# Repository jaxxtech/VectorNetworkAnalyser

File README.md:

View this project on [CADLAB.io](https://cadlab.io/project/1782). 

# VectorNetworkAnalyser

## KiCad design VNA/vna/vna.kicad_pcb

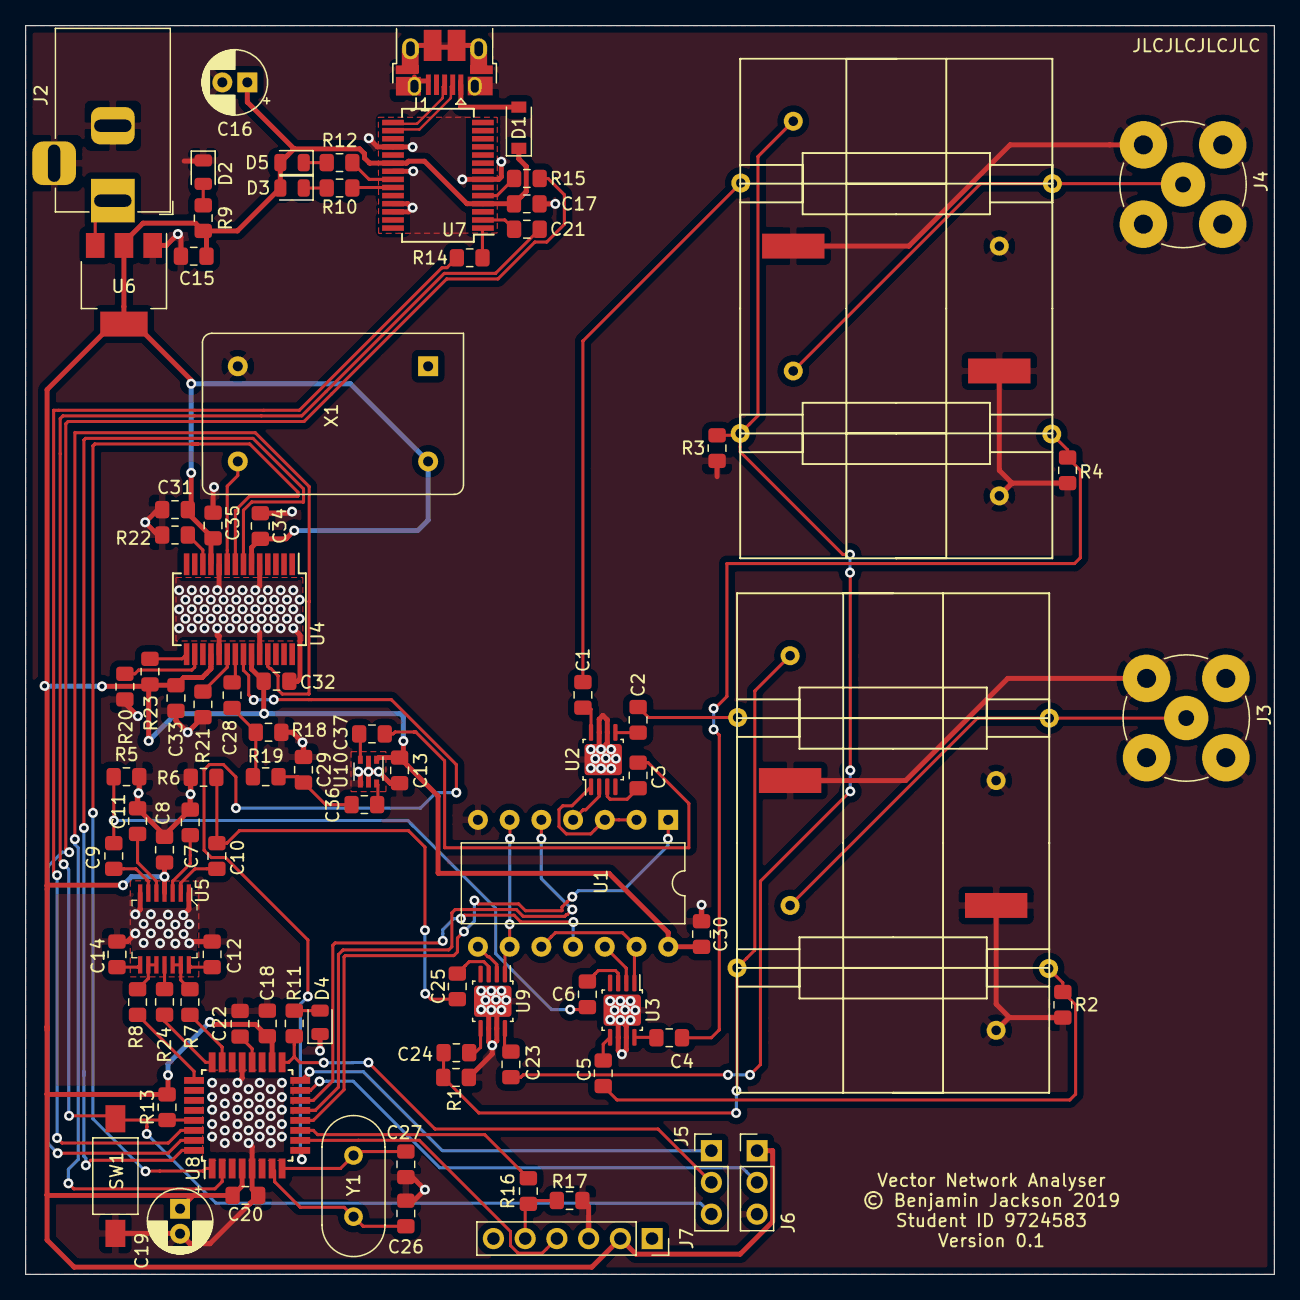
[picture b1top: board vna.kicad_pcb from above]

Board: 2 copper layers, 100.0 x 100.0 mm, 88 parts (0 on the bottom side), 82 nets.

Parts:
C1, C2, C3, C4, C5, C6, C17, C21, C22, C23, C24, C25, C28: 100n; C_0805_2012Metric_Pad1.15x1.40mm_HandSolder
C7, C8, C9, C10, C11, C29: 1n; C_0805_2012Metric_Pad1.15x1.40mm_HandSolder
C12, C14: DNP; C_0805_2012Metric_Pad1.15x1.40mm_HandSolder
C13, C36, C37: 470p; C_0805_2012Metric_Pad1.15x1.40mm_HandSolder
C15, C18, C20: 1u; C_0805_2012Metric_Pad1.15x1.40mm_HandSolder
C16, C19: 4.7u; CP_Radial_D5.0mm_P2.00mm
C26, C27: C0G 22p; C_0805_2012Metric_Pad1.15x1.40mm_HandSolder
C30, C32, C33, C34, C35: 0.1u; C_0805_2012Metric_Pad1.15x1.40mm_HandSolder
C31: 10u; C_0805_2012Metric_Pad1.15x1.40mm_HandSolder
D1: S4; D_SOD-123
D2: POWER_LED; LED_0805_2012Metric
D3: RX_LED; LED_0805_2012Metric
D4: onboard led; LED_0805_2012Metric
D5: TX_LED; LED_0805_2012Metric
HY1, HY2: Directional_Coupler
J1: USB_B_Micro; USB_Micro-B_Amphenol_10103594-0001LF_Horizontal
J2: DC_IN_Conn; BarrelJack_Horizontal
J3: Pt1; BNC_TEConnectivity_1478204_Vertical
J4: Pt2; BNC_TEConnectivity_1478204_Vertical
J5: ICSP 1,3,5; PinHeader_1x03_P2.54mm_Vertical
J6: ICSP 2,4,6; PinHeader_1x03_P2.54mm_Vertical
J7: Bluetooth Module Socket; PinSocket_1x06_P2.54mm_Vertical
R1, R2: 50 DNP; R_0805_2012Metric_Pad1.15x1.40mm_HandSolder
R3, R4: 50_DNP; R_0805_2012Metric_Pad1.15x1.40mm_HandSolder
R5, R6: 50; R_0805_2012Metric_Pad1.15x1.40mm_HandSolder
R7, R8, R24: 47; R_0805_2012Metric_Pad1.15x1.40mm_HandSolder
R9, R10, R11, R12, R13, R14, R15, R16, R20, R23: 1k; R_0805_2012Metric_Pad1.15x1.40mm_HandSolder
R17: 2k; R_0805_2012Metric_Pad1.15x1.40mm_HandSolder
R18: 16k; R_0805_2012Metric_Pad1.15x1.40mm_HandSolder
R19: 100m; R_0805_2012Metric_Pad1.15x1.40mm_HandSolder
R21: 25; R_0805_2012Metric_Pad1.15x1.40mm_HandSolder
R22: 3.9k; R_0805_2012Metric_Pad1.15x1.40mm_HandSolder
SW1: Reset; SW_SPST_FSMSM
U1: 74HCT04; DIP-14_W10.16mm
U2, U3, U9: HMC284; MSOP-8-1EP_3x3mm_P0.65mm_EP2.5x3mm_Mask1.73x2.36mm
U4: AD9851; SSOP-28_5.3x10.2mm_P0.65mm
U5: AD8302ARUZ; TSSOP-14_W4.4mm
U6: LM1117-5.0; SOT-223-3_TabPin2
U7: FT232RL; SSOP-28_5.3x10.2mm_P0.65mm
U8: ATmega328PB-AU; TQFP-32_7x7mm_P0.8mm
U10: BGA2851; SOT-363_SC-70-6
X1: 30MHz; Oscillator_DIP-14
Y1: 16MHz; Crystal_HC18-U_Vertical

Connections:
+5V: C8.2, C13.1, C15.1, C16.1, C17.1, C18.1, C19.1, C20.1, C30.1, C31.1, C32.1, C33.1, C34.1, C35.1, D1.1, D3.2, D5.2, J6.1, J7.2, R9.1, R13.1, R23.2, U1.14, U4.6, U4.11, U4.18, U4.23, U5.4, U6.2, U7.4, U7.20, U8.4, U8.18, U10.1, X1.14
/ACtrl: U1.5, U8.13
/Aref: C22.1, U8.20
/BCtrl: U1.11, U8.14
/ControlSystem.sch/AIN1_D7: R16.2, U8.11
/ControlSystem.sch/OC0A_AIN0_D6: J7.4, U8.10
/ControlSystem.sch/OC3A_RXD_D0: R14.2, U8.30
/ControlSystem.sch/OC4A_TXD_D1: R15.1, U8.31
/ControlSystem.sch/RESET: C21.1, J5.3, R13.2, SW1.1, U8.29
/ControlSystem.sch/RX: R14.1, U7.1
/ControlSystem.sch/RXD1_MISO_D12: J5.1, U8.16
/ControlSystem.sch/SCK_D13: J5.2, R11.1, U8.17
/ControlSystem.sch/TX: R15.2, U7.5
/ControlSystem.sch/TXD1_MOSI_OC2_D11: J6.2, U8.15
/D+: J1.3, U7.15
/D-: J1.2, U7.16
/DATA: U4.25, U8.2
/FQ_UD: U4.8, U8.1
/Fmeasured: C6.2, C9.2, R5.2
/Freference: C10.2, C25.2, R6.1
/Fwd_50ohm_A: C24.1, HY1.4, HY1.7, R1.1
/Fwd_50ohm_B: C23.1, HY2.4, HY2.7, R3.1
/PowerManagement/USB5V: D1.2, J1.1
/RF_RESET: U4.22, U8.9
/Receiver.sch/OffsetA: C7.1, U5.3
/Receiver.sch/VMag: R7.1, U8.23
/Receiver.sch/VPhase: R8.1, U8.25
/Receiver.sch/VRef(1v7): R24.1, U8.24
/Rev_50ohm_A: C5.1, HY1.6, R2.1
/Rev_50ohm_B: C4.1, HY2.6, R4.1
/SRC_50ohm: C3.2, C37.1
/SrcCtrl: U1.1, U8.12
/Src_50ohm_A: C2.1, HY1.1
/Src_50ohm_B: C1.1, HY2.1
/W_CLK: U4.7, U8.32
/pt1_50ohm: HY1.2, HY1.10, J3.1
/pt2_50ohm: HY2.2, HY2.10, J4.1
GND: C7.2, C8.1, C11.1, C12.1, C13.2, C14.2, C15.2, C16.2, C17.2, C18.2, C19.2, C20.2, C22.2, C26.1, C27.1, C29.2, C30.2, C31.2, C32.2, C33.2, C34.2, C35.2, D2.1, D4.1, HY1.3, HY1.5, HY1.8, HY1.9, HY2.3, HY2.5, HY2.8, HY2.9, J1.5, J1.6, J2.2, J2.3, J3.2, J4.2, J6.3, J7.3, R1.2, R2.2, R3.2, R4.2, R5.1, R6.2, R17.1, R18.2, R20.1, R21.1, R22.1, SW1.2, U1.7, U2.6, U2.7, U2.9, U3.6, U3.7, U3.9, U4.5, U4.10, U4.19, U4.24, U5.1, U5.7, U6.1, U7.7, U7.18, U7.21, U7.25, U7.26, U8.5, U8.21, U9.6, U9.7, U9.9, U10.2, U10.4, U10.5, X1.7
unnamed: C1.2, U2.8
unnamed: C2.2, U2.5
unnamed: C3.1, U2.3
unnamed: C4.2, U3.8
unnamed: C5.2, U3.5
unnamed: C6.1, U3.3
unnamed: C9.1, U5.6
unnamed: C10.1, U5.2
unnamed: C11.2, U5.5
unnamed: C12.2, U5.14
unnamed: C14.1, U5.8
unnamed: C21.2, U7.2
unnamed: C23.2, U9.8
unnamed: C24.2, U9.5
unnamed: C25.1, U9.3
unnamed: C26.2, U8.7, Y1.1
unnamed: C27.2, U8.8, Y1.2
unnamed: C28.1, R18.1, R19.1
unnamed: C28.2, U4.21
unnamed: C29.1, C36.2, R19.2
unnamed: C36.1, U10.6
unnamed: C37.2, U10.3
unnamed: D2.2, R9.2
unnamed: D3.1, R10.1
unnamed: D4.2, R11.2
unnamed: D5.1, R12.1
unnamed: J7.5, R16.1, R17.2
unnamed: R7.2, U5.12, U5.13
unnamed: R8.2, U5.9, U5.10
unnamed: R10.2, U7.23
unnamed: R12.2, U7.22
unnamed: R20.2, U4.16
unnamed: R21.2, U4.20
unnamed: R22.2, U4.12
unnamed: R23.1, U4.15
unnamed: R24.2, U5.11
unnamed: U1.2, U1.3, U2.1
unnamed: U1.4, U2.2
unnamed: U1.6, U1.9, U9.1
unnamed: U1.8, U9.2
unnamed: U1.10, U1.13, U3.1
unnamed: U1.12, U3.2
unnamed: U4.9, X1.8
VDC: J2.1, U6.3

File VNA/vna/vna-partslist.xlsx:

Id | Designator | Item | Quantity | Designation/value | rs stock no | unit cost | total | min qty |  | notes | ordering
1 | J9 | 15 pin 2.54mm pin header socket | 1 | vin_d13 |  |  | 0 |  |  |  | fset store
2 | J8 | 15 pin 2.54mm pin header socket | 1 | tx_d12 |  |  | 0 |  |  |  | fset store
3 | Y1 | QANTEK 16MHz Crystal ±20ppm HC-49/U-S 2-Pin, in pack of 10 | 1 | 16MHz | 814-9440 | 0.35 | 0.35 | 10 |  |  | rs components, or similar
4 | X1 | Clock Oscillator 5H14ET-30.000, 30 MHz, ±50ppm HCMOS, TTL 15pF, 14-Pin PDIP, 20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 | 1 | 30MHz | 767-5285 | 2.3199999999999998 | 2.3199999999999998 | 1 |  |  | rs components, or similar
5 | U9,U3,U2 | HMC284 RF Switch IC | 3 | HMC284 | 862-6310 | 4.1950000000000003 | 12.585000000000001 | 2 |  |  | from rs components
6 | U8 | Microchip Technology ATMEGA328P-AU, 8bit AVR Microcontroller, 20MHz, 32 kB Flas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 | 1 | ATmega328PB-AU | 131-0271 | 3.41 | 3.41 | 2 |  |  | fset store or rs components
7 | U7 | FTDI Chip FT232RL USB to Serial UART 3MBd, 28-Pin, SSOP | 1 | FT232RL | 406-580 | 8.0299999999999994 | 8.0299999999999994 | 1 |  |  | fset store or rs components
8 | U6 | Texas Instruments LM1117MP-5.0/NOPB, LDO Regulator, 800mA, 5 V, ±1% 3+Tab-Pin, 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 | 1 | LM1117-5.0 | 533-9583 | 1.56 | 1.56 | 1 |  |  | from fset store
9 | U5 | AD8302ARUZ Analog Devices, RF Amplifier Gain and Phase Detector 2-Channel, 14-P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 | 1 | AD8302ARUZ | 697-7262 | 34.86 | 34.86 | 1 |  |  | from rs components
10 | U4 | AD9851BRSZ, Direct Digital Synthesizer 10 bit-Bit 180000ksps, 28-Pin SSOP | 1 | AD9851 | 413-011 | 40.54 | 40.54 | 1 |  |  | from rs components
11 | U1 | NXP 74HCT04D,652, Hex Inverter, 4.5 ? 5.5 V, 14-Pin SOIC | 1 | 74HCT04 | 112-9988 | 0.51 | 0.51 | 1 |  |  | fset store or rs components
12 | SW1 | Surface mount SPDT push button Switch, normally open | 1 | Reset | 718-2477 | 0.4 | 0.4 | 5 |  |  | rs components or fset store
13 | R23,R20,R16,R15,R14,R13,R12,R11,R10,R9 | surface mount resistor | 10 | 1k |  |  |  |  |  |  | fset store
14 | R22 | surface mount resistor | 1 | 3.9k |  |  |  |  |  |  | fset store
15 | R21 | surface mount resistor | 1 | 25 |  |  |  |  |  |  | fset store
16 | R19,R18,R6,R5,R4,R3,R2,R1 | surface mount resistor | 8 | 50 |  |  |  |  |  |  | fset store
17 | R17 | surface mount resistor | 1 | 2k |  |  |  |  |  |  | fset store
18 | R8,R7 | surface mount resistor | 2 | 47 |  |  |  |  |  |  | fset store
19 | J7 | 6 pin 2.54mm pin header socket | 1 | Bluetooth Module Socket | 267-7400 | 1.022 | 1.022 | 5 |  | comes in runs of 20 pins | fset store
20 | J6 | 3 PinHeader_1x03_P2.54mm_Vertical | 1 | ICSP 2,4,6 | 547-3166 | 1.41 | 1.41 | 1 |  | run of 36 pins | fset store
21 | J5 | 3 PinHeader_1x03_P2.54mm_Vertical | 1 | ICSP 1,3,5 |  |  | 0 |  |  |  | fset store
22 | J4 | TE Connectivity Right Angle 50? PCB Mount BNC Connector, jack, Nickel, Through 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 | 1 | Pt2 | 616-3090 | 3.75 | 3.75 | 1 |  |  | rs components
23 | J3 | TE Connectivity Right Angle 50? PCB Mount BNC Connector, jack, Nickel, Through 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 | 1 | Pt1 | 616-3090 | 3.75 | 3.75 | 1 |  |  | rs components
24 | J2 | DC barrel jack, pcb mount | 1 | DC_IN_Conn | 122-4879 | 1.75 | 1.75 | 5 |  |  | rs components
25 | J1 | Amphenol FCI, Right Angle SMT, Type B Version 2.0 Micro USB Connector Receptacle | 1 | USB_B_Micro | 714-2347 | 1.05 | 1.05 | 5 |  |  | rs components
26 | HY2,HY1 | Directional_Coupler | 2 | Directional_Coupler | n/a | 0 | 0 | 0 |  | hand built | n/a
27 | D5 | SMD Chip LED - red | 1 | TX_LED |  |  | 0 |  |  |  | fset store
28 | D4 | SMD Chip LED - blue | 1 | onboard led |  |  | 0 |  |  |  | fset store
29 | D3 | SMD Chip LED - green | 1 | RX_LED |  |  | 0 |  |  |  | fset store
30 | D2 | SMD Chip LED - red | 1 | POWER_LED |  |  | 0 |  |  |  | fset store
31 | D1 | 40V schottky 350mA, Diode, 2-Pin SOD-323 | 1 | S4 |  |  | 0 |  |  |  | fset store or rs components
32 | C35,C34,C33,C32,C30 | Surface mount Capacitor | 5 | 0.1u |  |  | 0 |  |  |  | fset store
33 | C31 | Surface mount Capacitor | 1 | 10u |  |  | 0 |  |  |  | fset store
34 | C29 | Surface mount Capacitor | 1 | 330p |  |  | 0 |  |  |  | fset store
35 | C28 | Surface mount Capacitor | 1 | 330u |  |  | 0 |  |  |  | fset store
36 | C27,C26 | Surface mount Capacitor - timing circuit must be C0G | 2 | C0G 22p |  |  | 0 |  |  |  | fset store
37 | C25,C24,C23,C22,C21,C17,C6,C5,C4,C3,C2,C1 | Surface mount Capacitor | 12 | 100n |  |  | 0 |  |  |  | fset store
38 | C20,C18,C15 | Surface mount Capacitor | 3 | 1u |  |  | 0 |  |  |  | fset store
39 | C19,C16 | Surface mount Capacitor | 2 | 4.7u |  |  | 0 |  |  |  | fset store
40 | C14,C12 |  | 2 | DNP |  |  | 0 |  |  |  | n/a
41 | C13,C11,C10,C9,C8,C7 | Surface mount Capacitor | 6 | 1n |  |  | 0 |  |  |  | fset store
 |  |  |  |  |  | total cost | 117.297

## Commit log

2019-05-17 initial commit
    initial commit in order to test cadlab.io
2019-05-17 Backlink to CADLAB.io has been added.
2019-05-17 power and rf src blocks added
    battery managemet and rf source heirachical schematics have been added.
    these schematics are still empty however will server as a test for visual diff.
2019-05-17 main block editing
    main block schematic moved around to allow for better routing.
    power connectors and usb yet to be placed
    bluetooth module also not yet implemented
2019-05-21 block diagram for presentation completed
    at this stage i have completed the overall block diagram for the initial presentation.
    the blocks are mostly empty and require further development. the overall block diagram neglects power supply connections for clarity, these will be added internal to the blocks.
2019-05-23 adjusted main schematic to suit initial presentation
    i moved a few blocks around so that the cropped version of the block diagram would fit nicely in my semester 1 presentation
2019-06-01 changed inductors to a single transformer component
    inductors in the directional couplers was changed to a single transformer
    this will help with later layout opperations
2019-08-22 micro-controller pins labelled
    micro controller pins have been labelled, the pins on the bottom are yet to be linked to them.
    still to wire up ftdi chip,
    still to decide upon rf switch control schema.
2019-09-19 finished controller, chose compatible switches
    controller and rf switches have been completed.
    ToDo: finish filter design for RF Source, add auto gain control
    ToDo: finish directional coupler footprints
    ToDo: PCB Layout
2019-09-20 custom footprint for couplers, added decoupling caps
    added custom footprint for directional couplers - will need to verify it
    added decoupling caps to ad9851
2019-09-22 beginning pcb layout
    pcb layout process begun
2019-09-29 initial pcb design
    initial layout and grouping of components complete
2019-10-09 v0.1 completed, producing gerbers
    gerbers to be sent to jlc pcb pending their acceptance, they will be produced
2019-10-09 saved pcb file

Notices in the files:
VNA/vna/vna.kicad_pcb:
© Benjamin Jackson 2019
